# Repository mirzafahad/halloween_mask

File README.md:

# Halloween Mask

:star: Star me on GitHub — it helps!

Added the famous [Uncanny Eyes](https://learn.adafruit.com/animated-electronic-eyes) to a Mask. The PCB has three connectors for sensors:
- PIR conenctor
- I2C connector for any I2C capabale sensor
- LDR 

If you don't need want to use EL wire you can use the EL wire conenctor for other sensors, motors, relays etc.

Components used:
- [Adafruit ItsyBitsy M0](https://www.adafruit.com/product/3727)
- 2 x 1.44" [TFT Display](https://tinyurl.com/y4xz52jo)
- [Mask](https://tinyurl.com/y5uo26v6)
- [LDR](https://www.adafruit.com/product/161) 

More info: https://mirzafahad.github.io/2020-10-31-halloween-mask/

Youtube: https://youtu.be/H35RDPNnSZM

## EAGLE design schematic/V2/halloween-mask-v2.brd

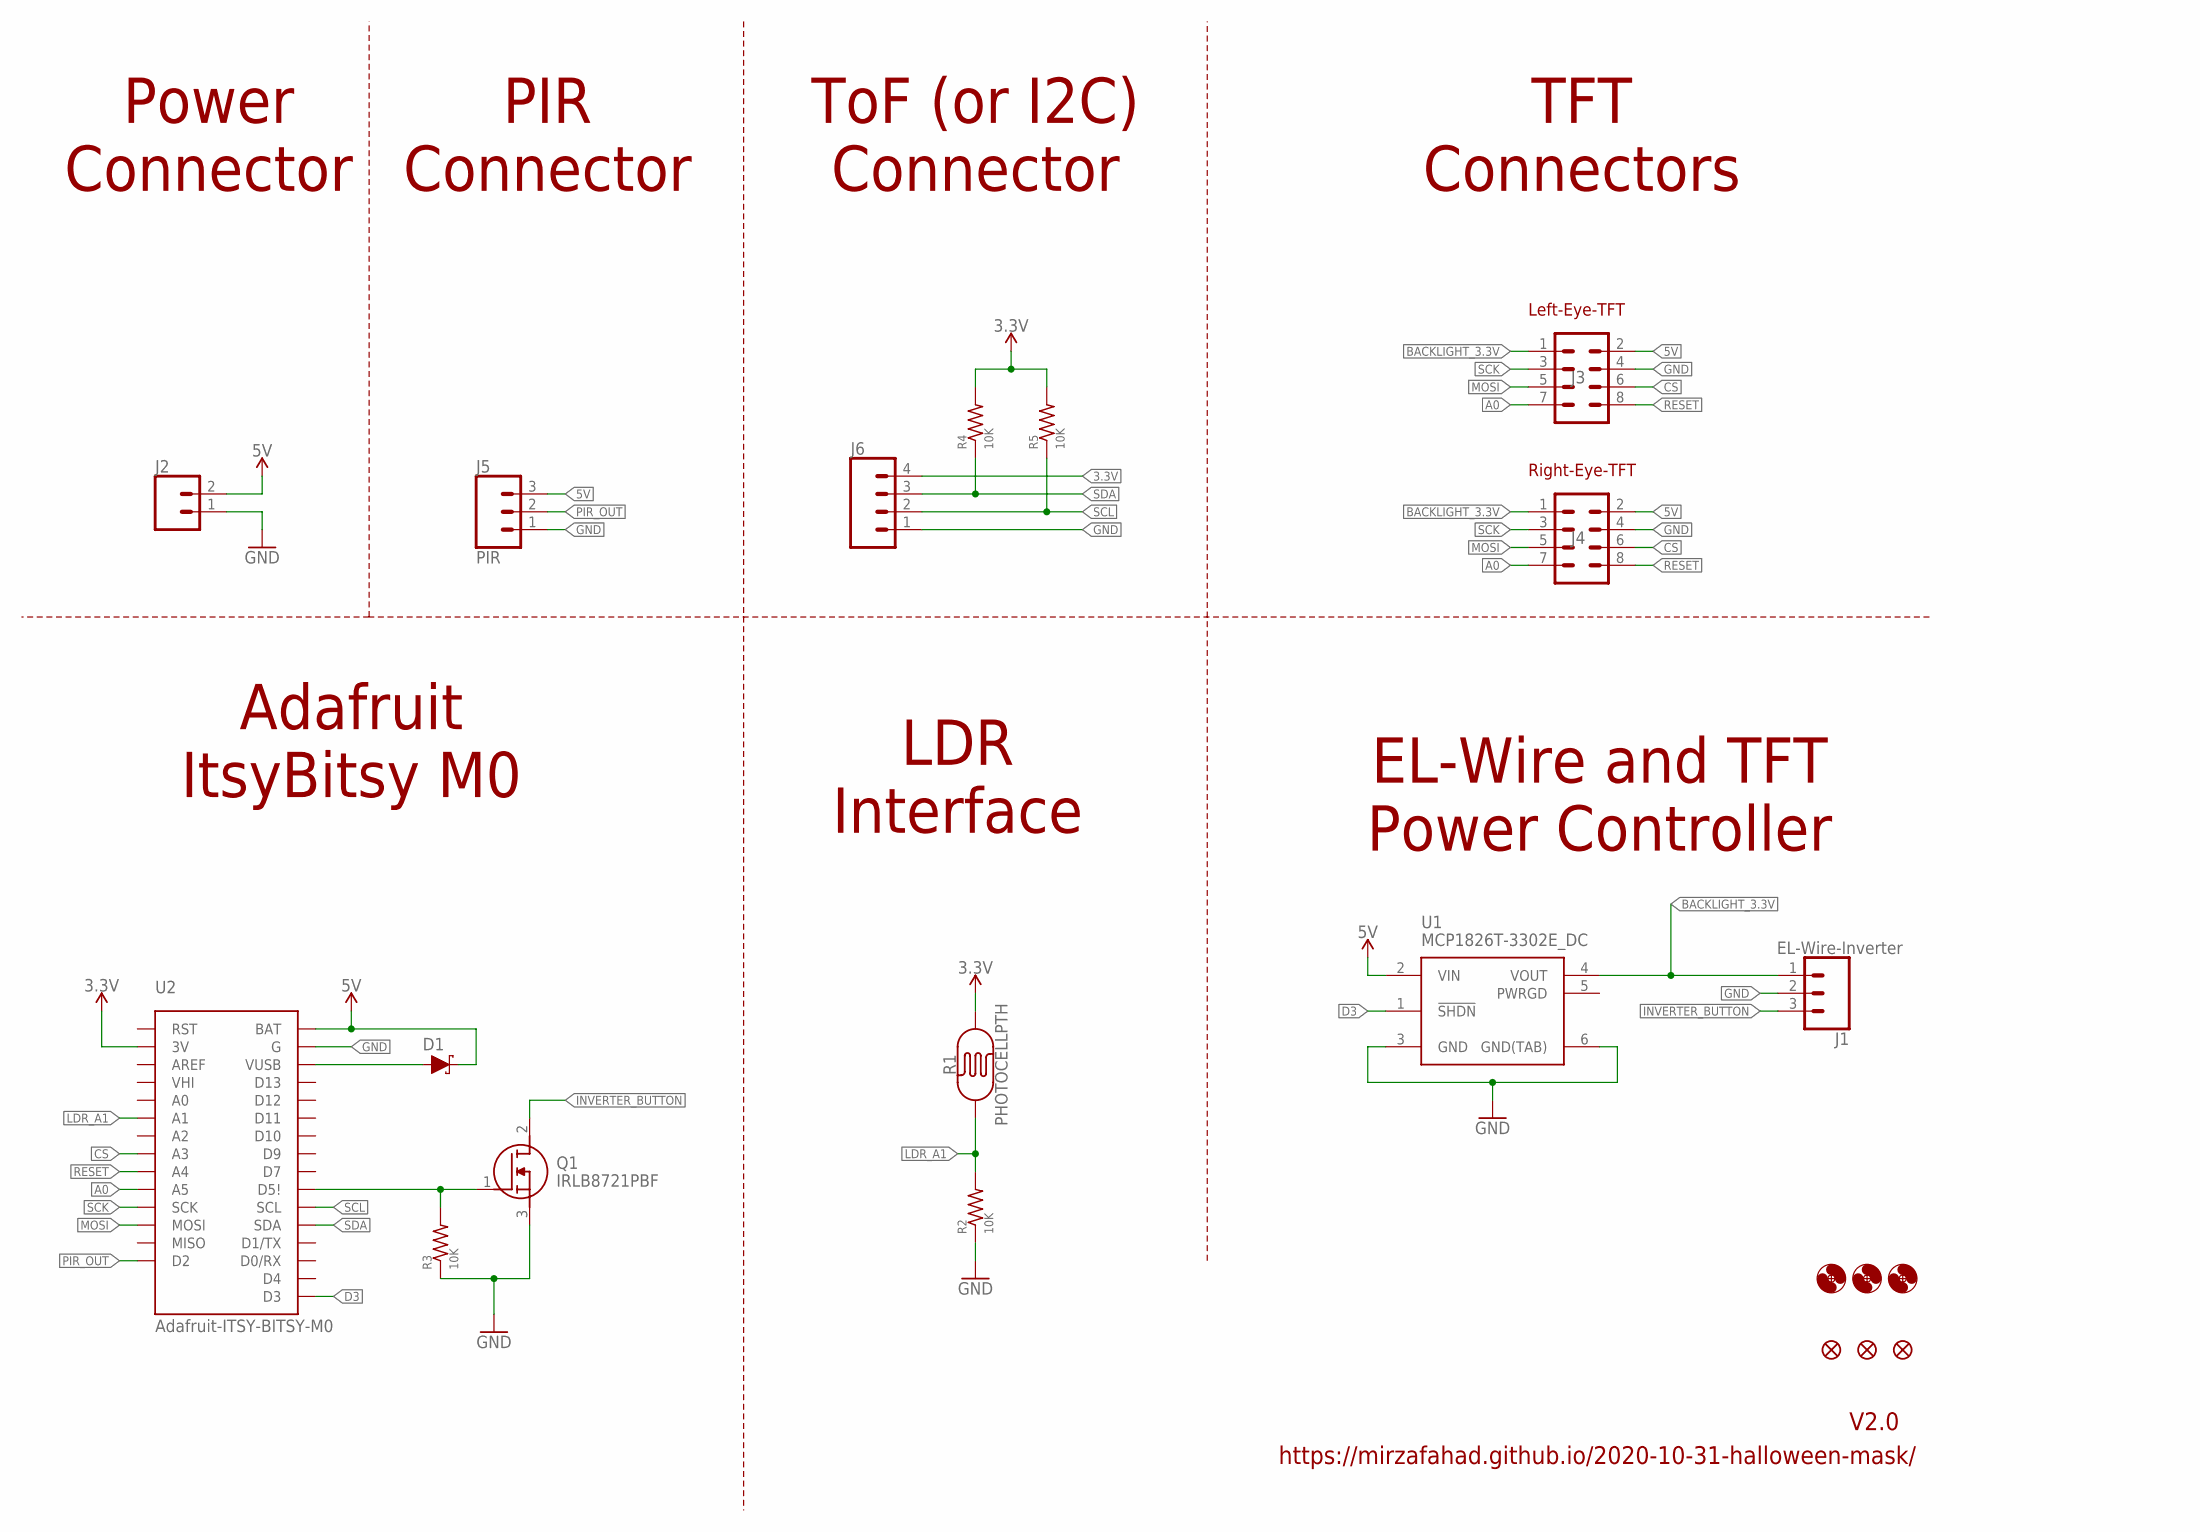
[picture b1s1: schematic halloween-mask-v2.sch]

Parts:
D1: DIODE-SCHOTTKY-MBR130T1G; SOD-123
FD1, FD2, FD3: FIDUCIAL0.2MM; FIDUCIAL-0.2MM
H1, H2, H4: MOUNT-HOLE2.8; 2,8
J1: EL-Wire-Inverter; 1X03
J2: CONN_02LOCK; 1X02_LOCK
J3, J4: CONN_04X2; 2X4
J5: PIR; 1X03_LOCK
J6: CONN_04PTH; 1X04
Q1: IRLB8721PBF; TO254P483X1016X1994-3P
R1: PHOTOCELLPTH; PHOTOCELL
R2, R3, R4, R5: 10K; R1206
U1: MCP1826T-3302E_DC; SOT127P706X180-6N
U2: Adafruit-ITSY-BITSY-M0; ITSY-BITSY-LESS-PINS

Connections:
3.3V: J6.4, R1.2, R4.2, R5.2, U2.P2 (3V)
5V: D1.2 (C), J2.2, J3.2, J4.2, J5.3, U1.2 (VIN), U2.P28 (BAT)
A0: J3.7, J4.7, U2.P10 (A5)
BACKLIGHT_3.3V: J1.1, J3.1, J4.1, U1.4 (VOUT)
CS: J3.6, J4.6, U2.P8 (A3)
D3: U1.1 (!SHDN), U2.18 (D3)
GND: J1.2, J2.1, J3.4, J4.4, J5.1, J6.1, Q1.3 (S), R2.1, R3.1, U1.3 (GND), U1.6 (GND(TAB)), U2.P27 (G)
INVERTER_BUTTON: J1.3, Q1.2 (D)
LDR_A1: R1.1, R2.2, U2.P6 (A1)
MOSI: J3.5, J4.5, U2.P12 (MOSI)
unnamed: D1.1 (A), U2.P26 (VUSB)
unnamed: Q1.1 (G), R3.2, U2.P19 (D5!)
PIR_OUT: J5.2, U2.P14 (D2)
RESET: J3.8, J4.8, U2.P9 (A4)
SCK: J3.3, J4.3, U2.P11 (SCK)
SCL: J6.2, R5.1, U2.P18 (SCL)
SDA: J6.3, R4.1, U2.P17 (SDA)

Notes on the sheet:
V2.0
TFT Connectors
Left-Eye-TFT
Right-Eye-TFT
ToF (or I2C) Connector
EL-Wire and TFT Power Controller
PIR Connector
Power Connector
LDR Interface
Adafruit ItsyBitsy M0
https://mirzafahad.github.io/2020-10-31-halloween-mask/

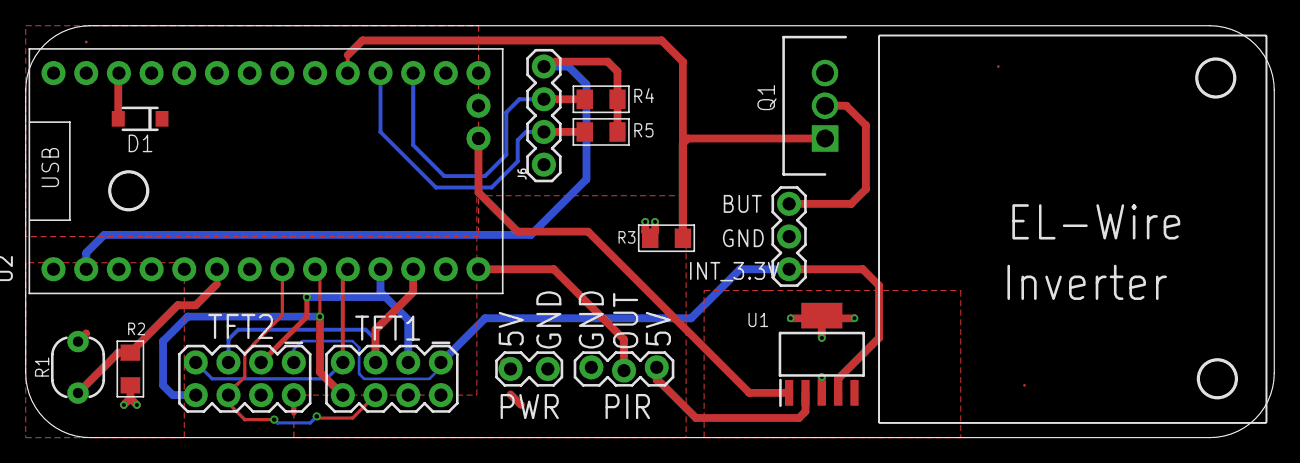
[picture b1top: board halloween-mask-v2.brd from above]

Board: 2 copper layers, 97.0 x 32.0 mm, 22 parts (0 on the bottom side), 17 nets.

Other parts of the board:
U$2: ELECTROCAT_LOGO_38X14MM

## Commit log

2020-10-31 Initial commit.
2020-10-31 Made necessary changes according to my circuit.
2020-10-31 Updated readme.
2020-10-31 updated gif.
2020-10-31 Updated readme with a link to my site.
2020-11-02 Added a connector for ToF. Added a schotky diode from Vusb to Vbat, so that I can both use external power and USB.
2021-03-21 Update readme.
2022-10-19 Changes made for a bigger display (240 x 320).
    Display link: https://www.adafruit.com/product/1743
2022-10-20 Made some changes according to Calvin's requirement.

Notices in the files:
README.md:
License: MIT
parts and their libraries:
SparkFun-Connectors: Licensing: Creative Commons ShareAlike 4.0 International - https://creativecommons.org/licenses/by-sa/4.0
